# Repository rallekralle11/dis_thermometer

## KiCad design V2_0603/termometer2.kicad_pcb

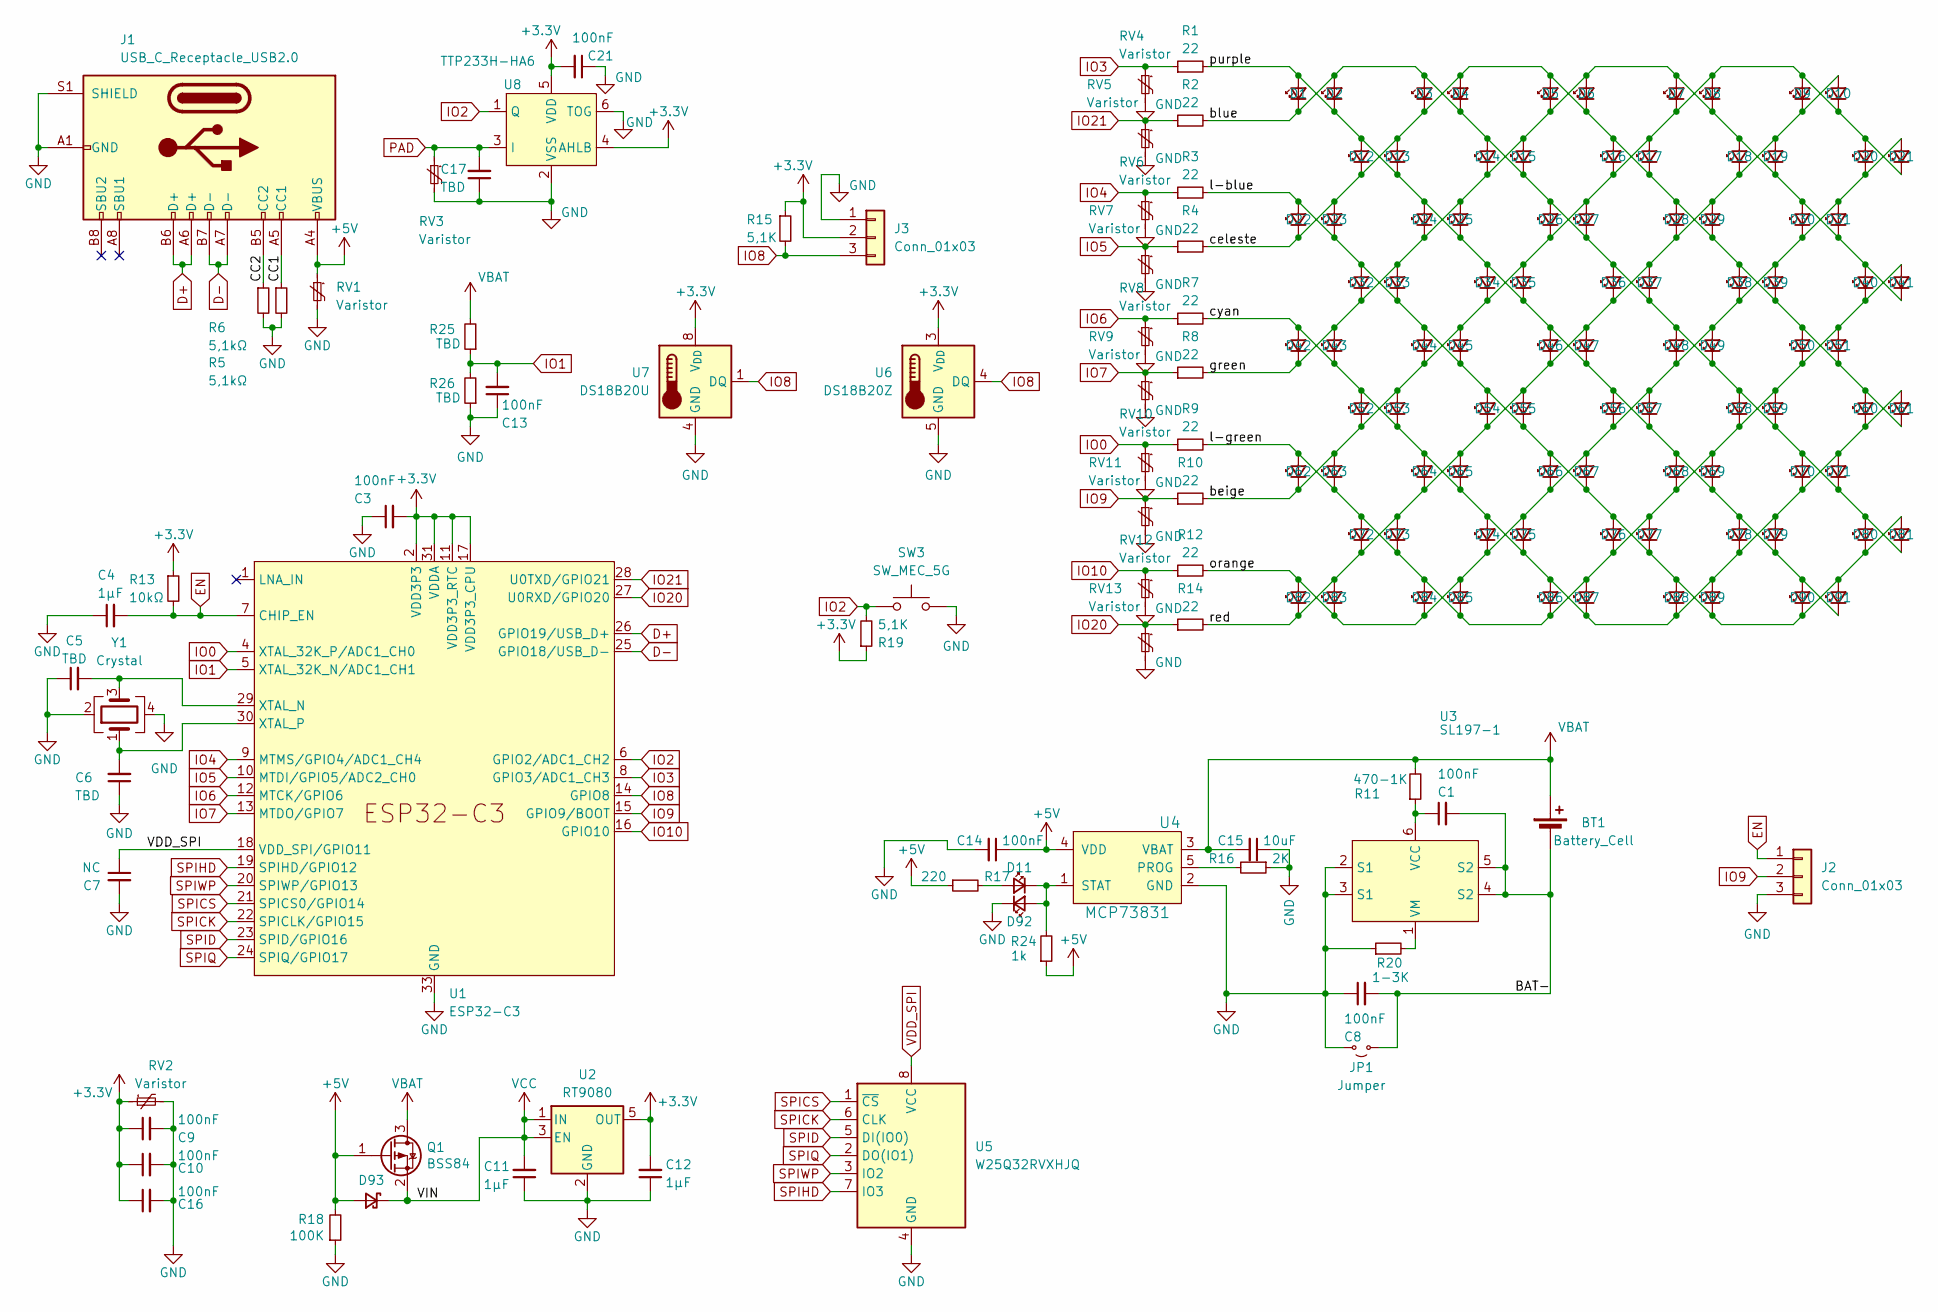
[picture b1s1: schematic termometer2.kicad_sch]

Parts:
BT1: Battery_Cell; BatteryHolder_MPD_BH-18650-PC2
C1, C3, C8, C9, C10, C13, C14, C16, C21: 100nF; C_0603_1608Metric
C4, C11, C12: 1µF; C_0603_1608Metric
C5, C6, C17: TBD; C_0603_1608Metric
C7: NC; C_0603_1608Metric
C15: 10uF; C_0603_1608Metric
D1, D2, D3, D4, D5, D6, D7, D8, D9, D10, D12, D13, D14, D15, D16, D17, D18, D19, D20, D21, D22, D23, D24, D25, D26, D27, D28, D29, D30, D31, D32, D33, D34, D35, D36, D37, D38, D39, D40, D41, D42, D43, D44, D45, D46, D47, D48, D49, D50, D51, D52, D53, D54, D55, D56, D57, D58, D59, D60, D61, D62, D63, D64, D65, D66, D67, D68, D69, D70, D71, D72, D73, D74, D75, D76, D77, D78, D79, D80, D81, D82, D83, D84, D85, D86, D87, D88, D89, D90, D91: LED_0603_1608Metric
D11, D92: LED_CHR; LED_0603_1608Metric
D93: D_Schottky_Small; D_SOD-323; LCSC C114023
J1: USB_C_Receptacle_USB2.0; USB_C_Receptacle_G-Switch_GT-USB-7010ASV
J2: Conn_01x03; PinHeader_1x03_P2.54mm_Vertical
J3: Conn_01x03; JST_XH_B3B-XH-A_1x03_P2.50mm_Vertical
JP1: Jumper; SolderJumper-2_P1.3mm_Open_RoundedPad1.0x1.5mm
Q1: BSS84; SOT-23; LCSC C85202
R1, R2, R3, R4, R7, R8, R9, R10, R12, R14: 22; R_0603_1608Metric
R5, R6: 5,1kΩ; R_0603_1608Metric
R11: 470-1K; R_0603_1608Metric
R13: 10kΩ; R_0603_1608Metric
R15, R19: 5,1K; R_0603_1608Metric
R16: 2K; R_0603_1608Metric
R17: 220; R_0603_1608Metric
R18: 100K; R_0603_1608Metric
R20: 1-3K; R_0603_1608Metric
R24: 1k; R_0603_1608Metric
R25, R26: TBD; R_0603_1608Metric
RV1, RV2, RV3, RV4, RV5, RV6, RV7, RV8, RV9, RV10, RV11, RV12, RV13: Varistor; R_0603_1608Metric
SW3: SW_MEC_5G; SW_SPST_B3S-1000
U1: ESP32-C3; QFN-32-1EP_5x5mm_P0.5mm_EP3.45x3.45mm
U2: RT9080; SOT-23-5
U3: SL197-1; DFN-6-1EP_2x2mm_P0.5mm_EP0.6x1.37mm
U4: MCP73831; SOT-23-5; LCSC C14879
U5: W25Q32RVXHJQ; Winbond_USON-8-1EP_3x2mm_P0.5mm_EP0.2x1.6mm
U6: DS18B20Z; SOIC-8_3.9x4.9mm_P1.27mm
U7: DS18B20U; MSOP-8_3x3mm_P0.65mm
U8: TTP233H-HA6; SOT-23-6
Y1: Crystal; Crystal_SMD_2016-4Pin_2.0x1.6mm

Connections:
+3.3V: C3.2, C9.1, C10.1, C12.2, C16.1, C21.2, J3.2, R13.1, R15.1, R19.1, RV2.1, U1.2 (VDD3P3), U1.3 (VDD3P3), U1.11 (VDD3P3_RTC), U1.17 (VDD3P3_CPU), U1.31 (VDDA), U1.32 (VDDA), U2.5 (OUT), U6.3 (V_{DD}), U7.8 (V_{DD}), U8.4 (AHLB), U8.5 (VDD)
+5V: C14.1, D93.2 (A), J1.A4 (VBUS), J1.A9 (VBUS), J1.B4 (VBUS), J1.B9 (VBUS), Q1.1 (G), R17.1, R18.2, R24.1, RV1.1, U4.4 (VDD)
/BAT-: BT1.2 (-), C1.2, C8.2, JP1.1 (A), U3.4 (S2), U3.5 (S2)
/CC1: J1.A5 (CC1), R6.1
/CC2: J1.B5 (CC2), R5.1
/beige: D7.1 (K), D8.2 (A), D9.2 (A), D10.1 (K), D16.1 (K), D17.2 (A), D20.2 (A), D21.1 (K), D26.1 (K), D27.2 (A), D34.1 (K), D35.2 (A), D44.1 (K), D45.2 (A), D52.1 (K), D53.2 (A), D62.1 (K), D63.2 (A), R10.2
/blue: D1.1 (K), D2.2 (A), D3.2 (A), D4.1 (K), D14.2 (A), D15.1 (K), D26.2 (A), D27.1 (K), D36.2 (A), D37.1 (K), D48.2 (A), D49.1 (K), D58.2 (A), D59.1 (K), D70.2 (A), D71.1 (K), D80.2 (A), D81.1 (K), R2.2
/celeste: D3.1 (K), D4.2 (A), D5.2 (A), D6.1 (K), D12.1 (K), D13.2 (A), D16.2 (A), D17.1 (K), D22.1 (K), D23.2 (A), D28.2 (A), D29.1 (K), D38.2 (A), D39.1 (K), D50.2 (A), D51.1 (K), D60.2 (A), D61.1 (K), R4.2
/cyan: D42.2 (A), D43.1 (K), D52.2 (A), D53.1 (K), D60.1 (K), D61.2 (A), D64.2 (A), D65.1 (K), D70.1 (K), D71.2 (A), D74.2 (A), D75.1 (K), D78.1 (K), D79.2 (A), D86.2 (A), D87.1 (K), D88.1 (K), D89.2 (A), R7.2
/green: D5.1 (K), D6.2 (A), D7.2 (A), D8.1 (K), D14.1 (K), D15.2 (A), D18.2 (A), D19.1 (K), D24.1 (K), D25.2 (A), D30.2 (A), D31.1 (K), D32.1 (K), D33.2 (A), D40.2 (A), D41.1 (K), D42.1 (K), D43.2 (A), R8.2
/l-blue: D22.2 (A), D23.1 (K), D32.2 (A), D33.1 (K), D44.2 (A), D45.1 (K), D54.2 (A), D55.1 (K), D66.2 (A), D67.1 (K), D76.2 (A), D77.1 (K), D80.1 (K), D81.2 (A), D88.2 (A), D89.1 (K), D90.1 (K), D91.2 (A), R3.2
/l-green: D40.1 (K), D41.2 (A), D50.1 (K), D51.2 (A), D58.1 (K), D59.2 (A), D62.2 (A), D63.1 (K), D68.1 (K), D69.2 (A), D72.2 (A), D73.1 (K), D76.1 (K), D77.2 (A), D84.2 (A), D85.1 (K), D86.1 (K), D87.2 (A), R9.2
/orange: D20.1 (K), D21.2 (A), D30.1 (K), D31.2 (A), D38.1 (K), D39.2 (A), D48.1 (K), D49.2 (A), D56.1 (K), D57.2 (A), D66.1 (K), D67.2 (A), D74.1 (K), D75.2 (A), D82.2 (A), D83.1 (K), D84.1 (K), D85.2 (A), R12.2
/purple: D1.2 (A), D2.1 (K), D12.2 (A), D13.1 (K), D24.2 (A), D25.1 (K), D34.2 (A), D35.1 (K), D46.2 (A), D47.1 (K), D56.2 (A), D57.1 (K), D68.2 (A), D69.1 (K), D78.2 (A), D79.1 (K), D90.2 (A), D91.1 (K), R1.2
/red: D9.1 (K), D10.2 (A), D18.1 (K), D19.2 (A), D28.1 (K), D29.2 (A), D36.1 (K), D37.2 (A), D46.1 (K), D47.2 (A), D54.1 (K), D55.2 (A), D64.1 (K), D65.2 (A), D72.1 (K), D73.2 (A), D82.1 (K), D83.2 (A), R14.2
D+: J1.A6 (D+), J1.B6 (D+), U1.26 (GPIO19/USB_D+)
D-: J1.A7 (D-), J1.B7 (D-), U1.25 (GPIO18/USB_D-)
EN: C4.2, J2.1, R13.2, U1.7 (CHIP_EN)
GND: C3.1, C4.1, C5.1, C6.1, C7.2, C8.1, C9.2, C10.2, C11.1, C12.1, C13.1, C14.2, C15.1, C16.2, C17.1, C21.1, D92.1 (K), J1.A1 (GND), J1.A12 (GND), J1.B1 (GND), J1.B12 (GND), J1.S1 (SHIELD), J2.3, J3.1, JP1.2 (B), R5.2, R6.2, R16.1, R18.1, R20.1, R26.1, RV1.2, RV2.2, RV3.2, RV4.2, RV5.2, RV6.2, RV7.2, RV8.2, RV9.2, RV10.2, RV11.2, RV12.2, RV13.2, SW3.3 (B), SW3.4 (B), U1.33 (GND), U2.2 (GND), U3.2 (S1), U3.3 (S1), U4.2 (GND), U5.4 (GND), U6.5 (GND), U7.4 (GND), U8.2 (VSS), U8.6 (TOG), Y1.2, Y1.4
IO0: R9.1, RV10.1, U1.4 (XTAL_32K_P/ADC1_CH0)
IO1: C13.2, R25.1, R26.2, U1.5 (XTAL_32K_N/ADC1_CH1)
IO2: R19.2, SW3.1 (A), SW3.2 (A), U1.6 (GPIO2/ADC1_CH2), U8.1 (Q)
IO3: R1.1, RV4.1, U1.8 (GPIO3/ADC1_CH3)
IO4: R3.1, RV6.1, U1.9 (MTMS/GPIO4/ADC1_CH4)
IO5: R4.1, RV7.1, U1.10 (MTDI/GPIO5/ADC2_CH0)
IO6: R7.1, RV8.1, U1.12 (MTCK/GPIO6)
IO7: R8.1, RV9.1, U1.13 (MTDO/GPIO7)
IO8: J3.3, R15.2, U1.14 (GPIO8), U6.4 (DQ), U7.1 (DQ)
IO9: J2.2, R10.1, RV11.1, U1.15 (GPIO9/BOOT)
IO10: R12.1, RV12.1, U1.16 (GPIO10)
IO20: R14.1, RV13.1, U1.27 (U0RXD/GPIO20)
IO21: R2.1, RV5.1, U1.28 (U0TXD/GPIO21)
unnamed: D11.2 (A), R17.2
unnamed: D11.1 (K), D92.2 (A), R24.2, U4.1 (STAT)
unnamed: C5.2, U1.29 (XTAL_N), Y1.3
unnamed: C6.2, U1.30 (XTAL_P), Y1.1
unnamed: C1.1, R11.1, U3.6 (VCC)
unnamed: R20.2, U3.1 (VM)
unnamed: R16.2, U4.5 (PROG)
PAD: C17.2, RV3.1, U8.3 (I)
SPICK: U1.22 (SPICLK/GPIO15), U5.6 (CLK)
SPICS: U1.21 (SPICS0/GPIO14), U5.1 (~CS)
SPID: U1.23 (SPID/GPIO16), U5.5 (DI(IO0))
SPIHD: U1.19 (SPIHD/GPIO12), U5.7 (IO3)
SPIQ: U1.24 (SPIQ/GPIO17), U5.2 (DO(IO1))
SPIWP: U1.20 (SPIWP/GPIO13), U5.3 (IO2)
VBAT: BT1.1 (+), C15.2, Q1.3 (D), R11.2, R25.2, U4.3 (VBAT)
VCC: C11.2, D93.1 (K), Q1.2 (S), U2.1 (IN), U2.3 (EN)
VDD_SPI: C7.1, U1.18 (VDD_SPI/GPIO11), U5.8 (VCC)

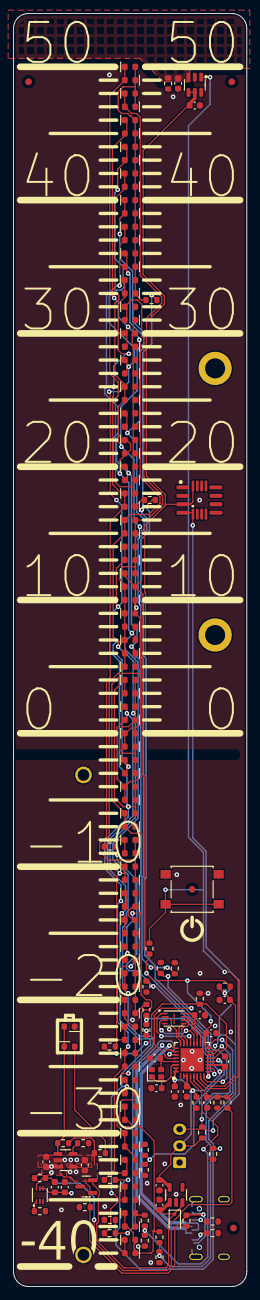
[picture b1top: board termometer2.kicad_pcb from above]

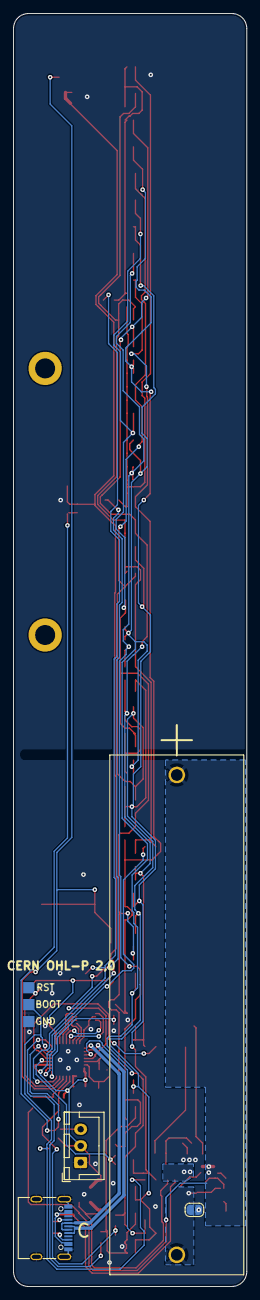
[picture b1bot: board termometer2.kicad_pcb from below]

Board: 2 copper layers, 35.0 x 191.0 mm, 168 parts (5 on the bottom side), 49 nets.

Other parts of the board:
FID1, FID2, FID3, FID4: Fiducial_1mm_Mask2mm
REF1, REF2: TestPoint_Loop_D3.80mm_Drill2.0mm

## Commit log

2024-09-18 init
2024-09-18 picture fix
2024-09-18 pictures etc
2024-10-07 code functional and some changes
2024-10-07 removed leftovers
2024-10-09 code
2024-11-07 code mostly
2024-12-08 info and stuff
2024-12-11 started on version 2 and included libraries with sketch
2025-01-25 cleanup

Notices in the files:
V2_0603/termometer2.kicad_pcb:
CERN OHL-P 2,0
